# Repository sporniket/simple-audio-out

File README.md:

# Simple Audio Out

> [WARNING] Please read carefully this note before using this project. It contains important facts.

Content

1. What is **Simple Audio Out**, and when to use it ?
2. What should you know before using **Simple Audio Out** ?
3. How to use **Simple Audio Out** ?
4. Known issues
5. Miscellanous

## 1. What is **Simple Audio Out**, and when to use it ?

**Simple Audio Out** is a simple audio output circuit for a 4 Ohm speaker, with volume setting 

### Licence

**Simple Audio Out** is published under the Creative Commons CC0 license. You can find a copy of the licence there : https://creativecommons.org/publicdomain/zero/1.0/legalcode

You can copy, modify, distribute and perform the work, even for commercial purposes, all without asking permission.

**Simple Audio Out** is distributed in the hope that it will be useful, but WITHOUT ANY WARRANTY; without even the implied warranty of MERCHANTABILITY or FITNESS FOR A PARTICULAR PURPOSE.

### Release notes

> No releases yet

## 2. What should you know before using **Simple Audio Out** ?

**Simple Audio Out** is made using Kicad 7.

> Do not use **Simple Audio Out** if this project is not suitable for your project.

## 3. How to use **Simple Audio Out** ?

### From sources

To get the latest available work, one must clone the git repository, build and install the package.

	git clone https://github.com/sporniket/simple-audio-out.git

Then, open the project with Kicad 7.

## 4. Known issues
See the [project issues](https://github.com/sporniket/simple-audio-out/issues) page.

## 5. Miscellanous

### Report issues
Use the [project issues](https://github.com/sporniket/simple-audio-out/issues) page.

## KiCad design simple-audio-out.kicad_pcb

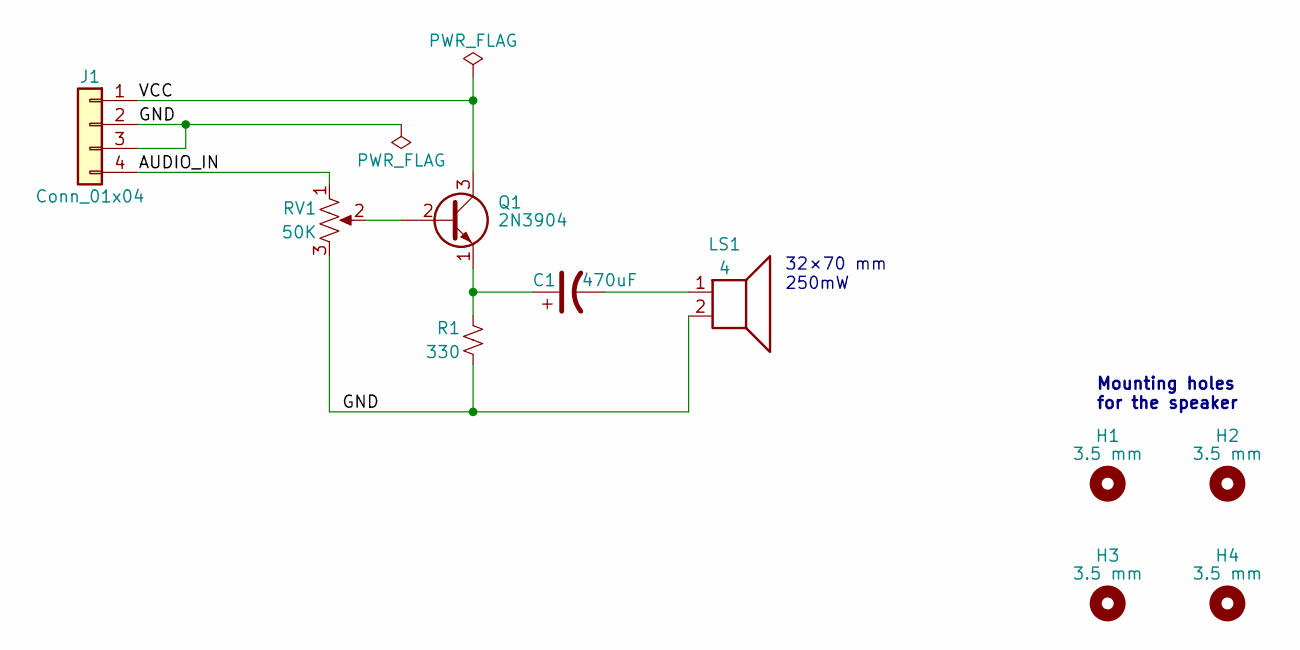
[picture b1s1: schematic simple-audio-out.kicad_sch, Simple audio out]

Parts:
C1: 470uF; CP_Radial_D10.0mm_P3.80mm
H1, H3: 3.5 mm; MountingHole_3.5mm_room_1.5mm
H2, H4: 3.5 mm; MountingHole_3.5mm
J1: Conn_01x04; PinHeader_1x04_P2.54mm_Horizontal
LS1: 4; PinHeader_1x02_P2.54mm_Horizontal
Q1: 2N3904; TO-92_Inline_Wide
R1: 330; Passive_THT_resistor_W2.54mm_L10.16mm
RV1: 50K; Potentiometer_Runtron_RM-065_Vertical

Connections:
/AUDIO_IN: J1.4, RV1.1
/GND: J1.2, J1.3, LS1.2, R1.2, RV1.3
/VCC: J1.1, Q1.3 (C)
unnamed: C1.2, LS1.1
unnamed: Q1.2 (B), RV1.2
unnamed: C1.1, Q1.1 (E), R1.1

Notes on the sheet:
Mounting holes for the speaker
32×70 mm 250mW

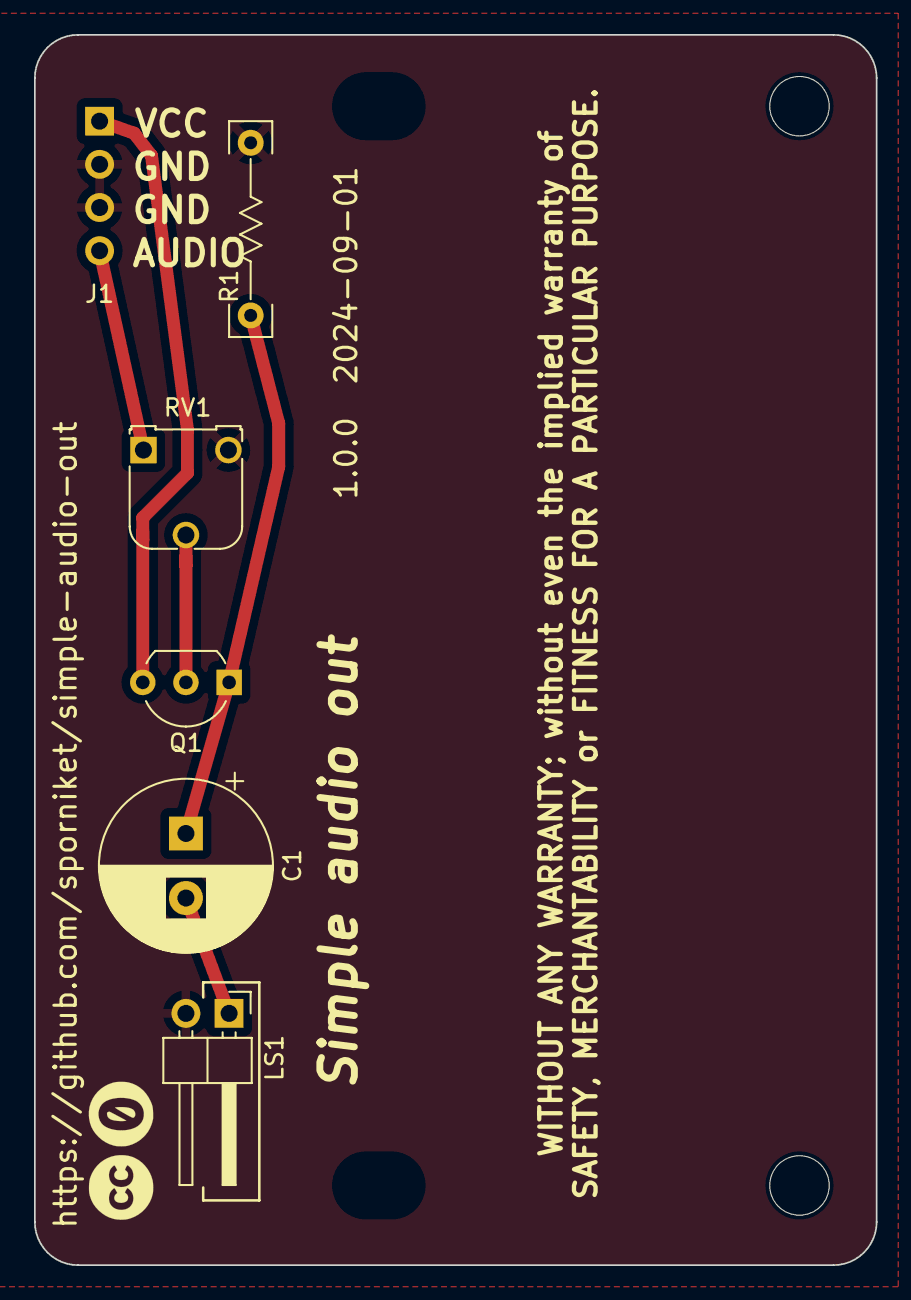
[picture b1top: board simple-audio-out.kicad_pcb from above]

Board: 2 copper layers, 49.5 x 72.4 mm, 10 parts (1 on the bottom side), 6 nets.

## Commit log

2024-01-20 init readme
2024-01-20 Done schematic
2024-01-20 add simple description in README
2024-01-21 revert to US symbols
2024-01-21 footprint assigned
2024-01-21 added mounting holes for speaker
2024-01-21 done PCB, ready to produce
2024-01-21 prepare release RC1
2024-09-01 #1 -- change the footprint of Q1 for easier assembly
2024-09-01 #1 -- adjust the mounting holes for the speaker
2024-09-01 #1 -- labels with project title, issue date, revision
2024-09-01 prepare next release
2024-09-04 add measurements on PCB
